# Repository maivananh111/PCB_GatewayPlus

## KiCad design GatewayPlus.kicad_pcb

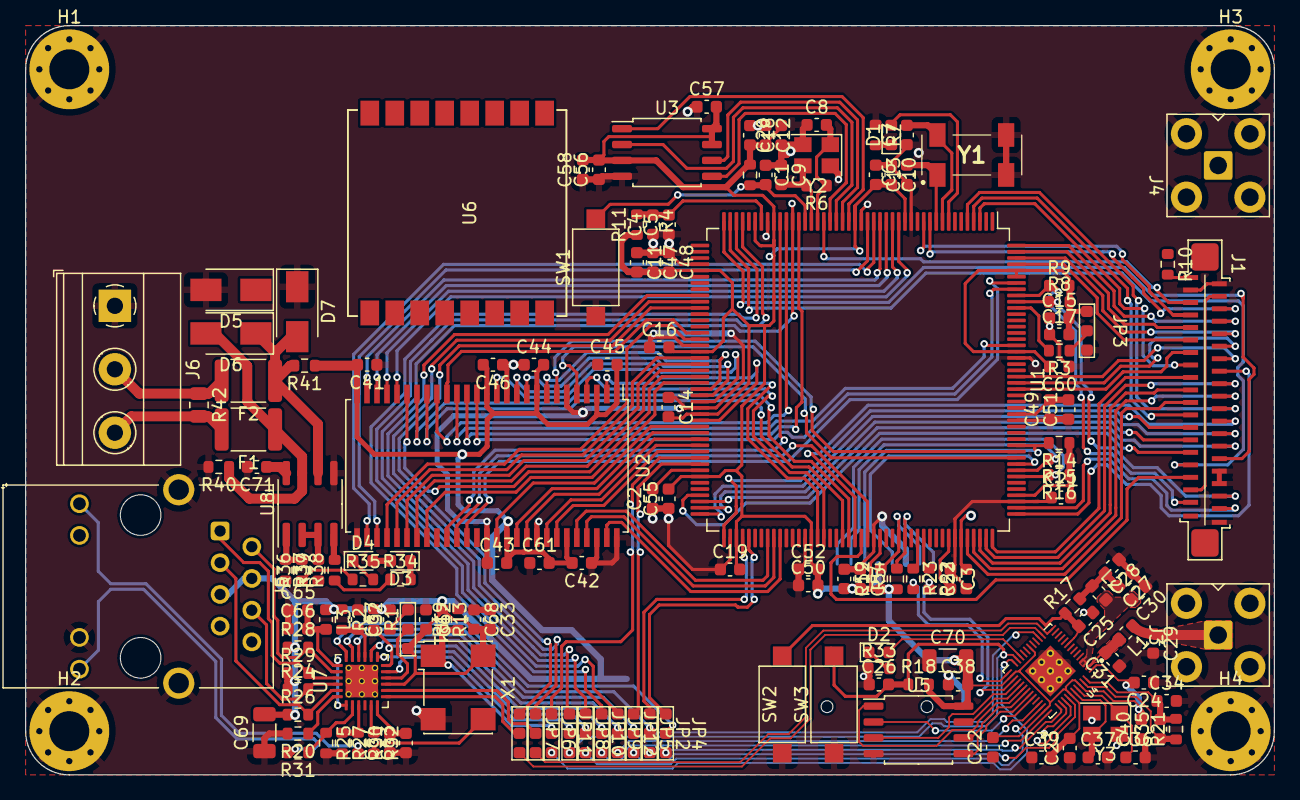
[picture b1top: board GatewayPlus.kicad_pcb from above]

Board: 2 copper layers, 100.0 x 60.0 mm, 162 parts (1 on the bottom side), 172 nets.

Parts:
C1, C2, C3, C4, C5, C8, C9, C25, C26, C32, C33, C62, C63, C64, C65, C66, C67, C68, C71: C_Small; C_0603_1608Metric
C6, C7: 22pF; C_0603_1608Metric
C10, C15, C16, C18, C22, C27, C38, C41, C44, C47, C50, C53, C56, C59: 1uF; C_0603_1608Metric
C11, C12, C13, C14, C17, C19, C20, C21, C23, C24, C28, C29, C30, C31, C34, C35, C36, C37, C39, C40, C42, C43, C45, C46, C48, C49, C51, C52, C54, C55, C57, C58, C60, C61: 100nF; C_0603_1608Metric
C69: C_Small; C_1206_3216Metric
C70: 10uF; C_1206_3216Metric
D1: LED; LED_0603_1608Metric
D2: LED_WIFI; LED_0603_1608Metric
D3: RS_Tx; LED_0603_1608Metric
D4: RS_Rx; LED_0603_1608Metric
D5, D6, D7: D_TVS; D_SMA
F1, F2: Fuse; Fuse_1812_4532Metric
H1, H2, H3, H4: Hole; MountingHole_3.2mm_M3_Pad_Via
J1: LTDC_LCD_FPC_40p; FPC_40p_Vertical
J2: Micro_SD_Card; MicroSD_Socket
J3: ESP Anten; Connector_Coaxial_SMA
J4: xAnt; Connector_Coaxial_SMA
J5: HR911105A; RJ45_Hanrun_HR911105A
J6: RS485; TerminalBlock_Phoenix_MKDS-1,5-3-5.08_1x03_P5.08mm_Horizont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
JP1: PHYADDR; Jump3_0603_Open
JP2: J_TXD0; Jump3_0603_Open
JP3: BOOT; Jump3_0603_Open
JP4: J_TXD1; Jump3_0603_Open
JP5: J_TXEN; Jump3_0603_Open
JP6: J_RXD0; Jump3_0603_Open
JP7: J_RXD1; Jump3_0603_Open
JP8: J_CRS_DV; Jump3_0603_Open
JP9: J_MDIO; Jump3_0603_Open
JP10: J_MDC; Jump3_0603_Open
JP11: J_CLKEN; Jump3_0603_Open
JP12: J_REFCLK; Jump3_0603_Open
L1, L2, L3: L_Small; L_0603_1608Metric
R1, R2, R3, R4, R5, R6, R7, R11, R12, R13, R14, R15, R16, R17, R18, R19, R20, R21, R22, R23, R24, R25, R26, R27, R28, R29, R30, R31, R32, R33, R34, R35, R36, R37, R38, R39, R40, R41: R_Small; R_0603_1608Metric
R8: 4k7; R_0603_1608Metric
R9: 4K7; R_0603_1608Metric
R10: 220; R_0603_1608Metric
R42: 120; R_0805_2012Metric
SW1: SW_Push; SW_SPST_CK_RS282G05A3
SW2: ESP_RESET; SW_SPST_CK_RS282G05A3
SW3: ESP_BOOT; SW_SPST_CK_RS282G05A3
U1: STM32F429IGTx; LQFP-176_24x24mm_P0.5mm
U2: IS42S16400J - HY57V641620E; TSOP-II-54_22.2x10.16mm_P0.8mm
U3: W25Q128JVS; SOIC-8_5.23x5.23mm_P1.27mm
U4: ESP32-D0WD-V3; ESP32-QFN48
U5: W25Q32JVSS; SOIC-8_5.23x5.23mm_P1.27mm
U6: Ai-Thinker-Ra-02; Ai-Thinker-Ra-01-LoRa
U7: LAN8720A; QFN-24-1EP_4x4mm_P0.5mm_EP2.6x2.6mm_ThermalVias
U8: MAX3485; SOIC-8_3.9x4.9mm_P1.27mm
X1: 50MHz; Oscillator_SMD_Abracon_ASV-4Pin_7.0x5.1mm
Y1: 32.768KHz; MC306327680KE3ROHS
Y2: 25MHz; Crystal_SMD_3225-4Pin_3.2x2.5mm
Y3: 40MHz; Crystal_SMD_3225-4Pin_3.2x2.5mm

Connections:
+3.3V: C10.2, C11.2, C12.2, C13.2, C14.2, C15.2, C16.2, C17.2, C18.2, C19.2, C20.2, C21.2, C22.2, C23.2, C24.2, C27.2, C28.2, C33.2, C38.2, C39.2, C40.2, C41.2, C42.2, C43.2, C44.2, C45.2, C46.2, C47.2, C48.2, C49.2, C50.2, C51.2, C52.2, C53.2, C54.2, C55.2, C56.2, C57.2, C58.2, C59.2, C60.2, C61.2, C62.2, C67.2, C68.2, C69.2, C70.2, C71.1, D3.2 (A), D4.2 (A), J1.4 (3V3), J1.35 (3V3), J2.4 (VDD), J5.4, J5.5, JP1.3 (B), JP3.1 (A), L2.1, L3.1, R1.1, R2.1, R4.2, R5.1, R8.2, R9.2, R11.1, R12.1, R13.1, R14.1, R15.1, R16.1, R17.2, R18.2, R24.1, R26.1, R28.1, R29.1, R39.2, R41.1, U1.15 (VDD), U1.23 (VDD), U1.36 (VDD), U1.39 (VDDA), U1.49 (VDD), U1.62 (VDD), U1.72 (VDD), U1.82 (VDD), U1.91 (VDD), U1.103 (VDD), U1.114 (VDD), U1.127 (VDD), U1.136 (VDD), U1.149 (VDD), U1.159 (VDD), U1.171 (PDR_ON), U1.172 (VDD), U2.1 (VDD), U2.3 (VDDQ), U2.9 (VDDQ), U2.14 (VDD), U2.27 (VDD), U2.43 (VDDQ), U2.49 (VDDQ), U3.3 (IO2), U3.7 (IO3), U3.8 (VCC), U4.1 (VDDA), U4.19 (VDD_RTC), U4.26 (VDD_SDIO), U4.37 (VDD_CPU), U4.43 (VDDA), U4.46 (VDDA), U5.8 (VCC), U7.9 (VDDIO), U8.8 (VCC), X1.4 (Vdd)
/ETH/ETH_CLKEN: JP11.2 (C), R13.2, R19.1, X1.1 (EN)
/ETH/ETH_REFCLK: JP12.2 (C), U7.14 (INT/REFCLKO)
/ETH/RMII_CRS_DV: JP8.2 (C), U7.11 (CRS_DV/MODE2)
/ETH/RMII_MDC: JP10.2 (C), U7.13 (MDC)
/ETH/RMII_MDIO: JP9.2 (C), R1.2, U7.12 (MDIO)
/ETH/RMII_RXD0: JP6.2 (C), U7.8 (RXD0/MODE0)
/ETH/RMII_RXD1: JP7.2 (C), U7.7 (RXD1/MODE1)
/ETH/RMII_TXD0: JP2.2 (C), U7.17 (TXD0)
/ETH/RMII_TXD1: JP4.2 (C), U7.18 (TXD1)
/ETH/RMII_TXEN: JP5.2 (C), U7.16 (TXEN)
/LTDC TFT LCD/LCD_BACKGROUND_LED: R10.1, U1.138 (PA15)
/LTDC TFT LCD/LTDC_B0: J1.15 (B0), U1.3 (PE4)
/LTDC TFT LCD/LTDC_B1: J1.14 (B1), U1.155 (PG12)
/LTDC TFT LCD/LTDC_B2: J1.13 (B2), U1.153 (PG10)
/LTDC TFT LCD/LTDC_B3: J1.12 (B3), U1.154 (PG11)
/LTDC TFT LCD/LTDC_B4: J1.11 (B4), U1.173 (PI4)
/LTDC TFT LCD/LTDC_B5: J1.10 (B5), U1.174 (PI5)
/LTDC TFT LCD/LTDC_B6: J1.9 (B6), U1.175 (PI6)
/LTDC TFT LCD/LTDC_B7: J1.8 (B7), U1.176 (PI7)
/LTDC TFT LCD/LTDC_DE: J1.5 (DE), U1.28 (PF10)
/LTDC TFT LCD/LTDC_G0: J1.23 (G0), U1.4 (PE5)
/LTDC TFT LCD/LTDC_G1: J1.22 (G1), U1.5 (PE6)
/LTDC TFT LCD/LTDC_G2: J1.21 (G2), U1.128 (PH13)
/LTDC TFT LCD/LTDC_G3: J1.20 (G3), U1.129 (PH14)
/LTDC TFT LCD/LTDC_G4: J1.19 (G4), U1.130 (PH15)
/LTDC TFT LCD/LTDC_G5: J1.18 (G5), U1.131 (PI0)
/LTDC TFT LCD/LTDC_G6: J1.17 (G6), U1.132 (PI1)
/LTDC TFT LCD/LTDC_G7: J1.16 (G7), U1.133 (PI2)
/LTDC TFT LCD/LTDC_HSYNC: J1.7 (HSYNC), U1.12 (PI10)
/LTDC TFT LCD/LTDC_PCLK: J1.33 (PCLK), U1.111 (PG7)
/LTDC TFT LCD/LTDC_R0: J1.31 (R0), U1.43 (PH2)
/LTDC TFT LCD/LTDC_R1: J1.30 (R1), U1.44 (PH3)
/LTDC TFT LCD/LTDC_R2: J1.29 (R2), U1.85 (PH8)
/LTDC TFT LCD/LTDC_R3: J1.28 (R3), U1.86 (PH9)
/LTDC TFT LCD/LTDC_R4: J1.27 (R4), U1.87 (PH10)
/LTDC TFT LCD/LTDC_R5: J1.26 (R5), U1.88 (PH11)
/LTDC TFT LCD/LTDC_R6: J1.25 (R6), U1.89 (PH12)
/LTDC TFT LCD/LTDC_R7: J1.24 (R7), U1.110 (PG6)
/LTDC TFT LCD/LTDC_VSYNC: J1.6 (VSYNC), U1.11 (PI9)
/LTDC TFT LCD/TOUCH_INT: J1.38 (T_INT), U1.134 (PI3)
/LTDC TFT LCD/TOUCH_SCL: J1.36 (T_SCL), R8.1, U1.167 (PB8)
/LTDC TFT LCD/TOUCH_SDA: J1.37 (T_SDA), R9.1, U1.168 (PB9)
/MCU/ETH_CLKEN: JP11.1 (A), U1.79 (PB10)
/MCU/ETH_REFCLK: JP12.1 (A), U1.41 (PA1)
/MCU/FLASH_CS: U1.24 (PF6), U3.1 (~CS)
/MCU/RMII_CRS_DV: JP8.1 (A), U1.53 (PA7)
/MCU/RMII_MDC: JP10.1 (A), U1.33 (PC1)
/MCU/RMII_MDIO: JP9.1 (A), U1.42 (PA2)
/MCU/RMII_RXD0: JP6.1 (A), U1.54 (PC4)
/MCU/RMII_RXD1: JP7.1 (A), U1.55 (PC5)
/MCU/RMII_TXD0: JP2.1 (A), U1.92 (PB12)
/MCU/RMII_TXD1: JP4.1 (A), U1.93 (PB13)
/MCU/RMII_TXEN: JP5.1 (A), U1.80 (PB11)
/MCU/SDIO_CLK: J2.5 (CLK), U1.141 (PC12)
/MCU/SDIO_CMD: J2.3 (CMD), R14.2, U1.144 (PD2)
/MCU/SDIO_D0: J2.7 (DAT0), R12.2, U1.117 (PC8)
/MCU/SDIO_D1: J2.8 (DAT1), R5.2, U1.118 (PC9)
/MCU/SDIO_D2: J2.1 (DAT2), R16.2, U1.139 (PC10)
/MCU/SDIO_D3: J2.2 (DAT3/CD), R15.2, U1.140 (PC11)
/MCU/SDRAM_A0: U1.16 (PF0), U2.23 (A0)
/MCU/SDRAM_A1: U1.17 (PF1), U2.24 (A1)
/MCU/SDRAM_A2: U1.18 (PF2), U2.25 (A2)
/MCU/SDRAM_A3: U1.19 (PF3), U2.26 (A3)
/MCU/SDRAM_A4: U1.20 (PF4), U2.29 (A4)
/MCU/SDRAM_A5: U1.21 (PF5), U2.30 (A5)
/MCU/SDRAM_A6: U1.60 (PF12), U2.31 (A6)
/MCU/SDRAM_A7: U1.63 (PF13), U2.32 (A7)
/MCU/SDRAM_A8: U1.64 (PF14), U2.33 (A8)
/MCU/SDRAM_A9: U1.65 (PF15), U2.34 (A9)
/MCU/SDRAM_A10: U1.66 (PG0), U2.22 (A10)
/MCU/SDRAM_A11: U1.67 (PG1), U2.35 (A11)
/MCU/SDRAM_BA0: U1.108 (PG4), U2.20 (BA0)
/MCU/SDRAM_BA1: U1.109 (PG5), U2.21 (BA1)
/MCU/SDRAM_CKE: U1.35 (PC3), U2.37 (CKE)
/MCU/SDRAM_CLK: U1.112 (PG8), U2.38 (CLK)
/MCU/SDRAM_D0: U1.104 (PD14), U2.2 (DQ0)
/MCU/SDRAM_D1: U1.105 (PD15), U2.4 (DQ1)
/MCU/SDRAM_D2: U1.142 (PD0), U2.5 (DQ2)
/MCU/SDRAM_D3: U1.143 (PD1), U2.7 (DQ3)
/MCU/SDRAM_D4: U1.68 (PE7), U2.8 (DQ4)
/MCU/SDRAM_D5: U1.69 (PE8), U2.10 (DQ5)
/MCU/SDRAM_D6: U1.70 (PE9), U2.11 (DQ6)
/MCU/SDRAM_D7: U1.73 (PE10), U2.13 (DQ7)
/MCU/SDRAM_D8: U1.74 (PE11), U2.42 (DQ8)
/MCU/SDRAM_D9: U1.75 (PE12), U2.44 (DQ9)
/MCU/SDRAM_D10: U1.76 (PE13), U2.45 (DQ10)
/MCU/SDRAM_D11: U1.77 (PE14), U2.47 (DQ11)
/MCU/SDRAM_D12: U1.78 (PE15), U2.48 (DQ12)
/MCU/SDRAM_D13: U1.96 (PD8), U2.50 (DQ13)
/MCU/SDRAM_D14: U1.97 (PD9), U2.51 (DQ14)
/MCU/SDRAM_D15: U1.98 (PD10), U2.53 (DQ15)
/MCU/SDRAM_NBL0: U1.169 (PE0), U2.15 (LDQM)
/MCU/SDRAM_NBL1: U1.170 (PE1), U2.39 (UDQM)
/MCU/SDRAM_NCAS: U1.160 (PG15), U2.17 (~CAS)
/MCU/SDRAM_NE: U1.34 (PC2), U2.19 (~CS)
/MCU/SDRAM_NRAS: U1.59 (PF11), U2.18 (~RAS)
/MCU/SDRAM_NWE: U1.32 (PC0), U2.16 (~WE)
/MCU/SPI1_MISO: U1.26 (PF8), U3.2 (DO(IO1))
/MCU/SPI1_MOSI: U1.27 (PF9), U3.5 (DI(IO0))
/MCU/SPI1_SCK: U1.25 (PF7), U3.6 (CLK)
/MCU/USART1_RX: R22.1, U1.121 (PA10)
/MCU/USART1_TX: R23.1, U1.120 (PA9)
/RS485/A+: F2.2, J6.2, R42.1
/RS485/B-: F1.2, J6.3, R42.2
/RS485/Rx: R35.1, R36.1
/RS485/Tx: R34.1, R38.1
/WIFI ESP32/ETH_CLKEN: JP11.3 (B), U4.24 (GPIO4)
/WIFI ESP32/ETH_REFCLK: C26.2, JP12.3 (B), R18.1, SW3.2, U4.23 (GPIO0)
/WIFI ESP32/F_CLK: U4.31 (SD_CLK), U5.6 (CLK)
/WIFI ESP32/F_CMD: U4.30 (SD_CMD), U5.1 (~CS)
/WIFI ESP32/F_D0: U4.32 (SD_D0), U5.5 (DI(IO0))
/WIFI ESP32/F_D1: U4.33 (SD_D1), U5.2 (DO(IO1))
/WIFI ESP32/F_D2: U4.28 (SD_D2), U5.3 (IO2)
/WIFI ESP32/F_D3: U4.29 (SD_D3), U5.7 (IO3)
/WIFI ESP32/RMII_CRSDV: JP8.3 (B), U4.16 (GPIO27)
/WIFI ESP32/RMII_MDC: JP10.3 (B), U4.36 (GPIO23)
/WIFI ESP32/RMII_MDIO: JP9.3 (B), U4.35 (GPIO18)
/WIFI ESP32/RMII_RXD0: JP6.3 (B), U4.14 (GPIO25)
/WIFI ESP32/RMII_RXD1: JP7.3 (B), U4.15 (GPIO26)
/WIFI ESP32/RMII_TXD0: JP2.3 (B), U4.38 (GPIO19)
/WIFI ESP32/RMII_TXD1: JP4.3 (B), U4.39 (GPIO22)
/WIFI ESP32/RMII_TXEN: JP5.3 (B), U4.42 (GPIO21)
BOOT0: JP3.2 (C), R3.1
GND: C1.1, C2.1, C3.1, C4.1, C5.1, C6.1, C7.1, C8.1, C9.1, C10.1, C11.1, C12.1, C13.1, C14.1, C15.1, C16.1, C17.1, C18.1, C19.1, C20.1, C21.1, C22.1, C23.1, C24.1, C25.1, C26.1, C27.1, C28.1, C29.2, C30.1, C31.1, C32.1, C33.1, C34.2, C36.2, C37.2, C38.1, C39.1, C40.1, C41.1, C42.1, C43.1, C44.1, C45.1, C46.1, C47.1, C48.1, C49.1, C50.1, C51.1, C52.1, C53.1, C54.1, C55.1, C56.1, C57.1, C58.1, C59.1, C60.1, C61.1, C62.1, C63.1, C64.1, C65.1, C66.1, C67.1, C68.1, C69.1, C70.1, C71.2, D5.2 (A2), D7.1 (A1), H1.1, H2.1, H3.1, H4.1, J1.2 (LED-), J1.3 (GND), J1.32 (GND), J1.34 (GND), J1.40 (GND), J2.6 (VSS), J2.9 (SHIELD), J3.2 (Ext), J4.2 (Ext), J5.8, J5.11, J5.SH (SHIELD), J6.1, JP1.1 (A), JP3.3 (B), R7.1, R19.2, R20.2, R25.2, R27.2, R33.1, R40.2, SW1.1, SW2.1, SW3.1, U1.14 (VSS), U1.22 (VSS), U1.37 (VSSA), U1.48 (BYPASS_REG), U1.61 (VSS), U1.71 (VSS), U1.90 (VSS), U1.102 (VSS), U1.113 (VSS), U1.126 (VSS), U1.135 (VSS), U1.148 (VSS), U1.158 (VSS), U2.6 (GNDQ), U2.12 (GNDQ), U2.28 (GND), U2.41 (GND), U2.46 (GNDQ), U2.52 (GNDQ), U2.54 (GND), U3.4 (GND), U4.49 (GND_PAD), U5.4 (GND), U7.25 (VSS), U8.5 (GND), X1.2 (GND), Y1.2, Y1.3, Y2.2, Y2.4, Y3.2, Y3.4
HSEI: C8.2, R6.1, U1.29 (PH0), Y2.1
HSEO: C9.2, R6.2, U1.30 (PH1), Y2.3
LSEI: C7.2, U1.9 (PC14), Y1.4
LSEO: C6.2, U1.10 (PC15), Y1.1
unnamed: C1.2, R4.1, SW1.2, U1.31 (NRST)
unnamed: C2.2, U1.81 (VCAP_1)
unnamed: C3.2, U1.125 (VCAP_2)
unnamed: C4.2, C5.2, R11.2, U1.38 (VREF+)
unnamed: C25.2, R17.1, SW2.2, U4.9 (CHIP_PU)
unnamed: C29.1, J3.1 (In), L1.1
unnamed: C30.2, L2.2, U4.3 (VDD), U4.4 (VDD)
unnamed: C31.2, L1.2, U4.2 (LNA_IN)
unnamed: C32.2, R2.2, U7.15 (RST)
unnamed: C34.1, C35.2, R21.2, U4.48 (CAP1)
unnamed: C35.1, R21.1, U4.47 (CAP2)
unnamed: C36.1, U4.45 (XTAL_P), Y3.1
unnamed: C37.1, U4.44 (XTAL_N), Y3.3
unnamed: C63.2, C64.2, U7.6 (VDDCR)
unnamed: C65.2, C66.2, L3.2, U7.1 (VDD2A), U7.19 (VDD1A)
unnamed: D1.1 (K), R7.2
unnamed: D2.1 (K), R33.2
unnamed: D2.2 (A), U4.22 (GPIO2)
unnamed: D3.1 (K), R34.2
unnamed: D4.1 (K), R35.2
unnamed: D5.1 (A1), D6.2 (A2), F1.1, R40.1, U8.7 (B)
unnamed: D6.1 (A1), D7.2 (A2), F2.1, R41.2, U8.6 (A)
unnamed: J1.1 (LED+), R10.2
unnamed: J5.1, R29.2, U7.21 (TXP)
unnamed: J5.2, R28.2, U7.20 (TXN)
unnamed: J5.3, R26.2, U7.23 (RXP)
unnamed: J5.6, R24.2, U7.22 (RXN)
unnamed: J5.9, R30.2
unnamed: J5.12, R31.2
unnamed: JP1.2 (C), U7.10 (RXER/PHYAD0)
unnamed: R3.2, U1.166 (BOOT0)
unnamed: R20.1, U7.24 (RBIAS)
unnamed: R22.2, U4.27 (GPIO17)
unnamed: R23.2, U4.25 (GPIO16)
unnamed: R25.1, R31.1, U7.2 (LED2/nINTSEL)
unnamed: R27.1, R30.1, U7.3 (LED1/REGOFF)
unnamed: R32.1, U7.5 (XTAL1/CLKIN)
unnamed: R32.2, X1.3 (OUT)
unnamed: R36.2, R39.1, U8.1 (RO)
unnamed: R37.2, U8.2 (~RE), U8.3 (DE)
unnamed: R38.2, U8.4 (DI)
unnamed: U6.1 (GND), U6.2 (GND), U6.9 (GND), U6.16 (GND)
STATUS LED: D1.2 (A), U1.8 (PC13)

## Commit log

2023-02-06 MCU, FLASH, SDRAM, LCD.
2023-02-09 Add WiFi block and finished WiFi layout
2023-02-10 Add Ethernet LAN8720 Layout.
2023-02-11 Finish Ethernet Layout.
2023-02-11 Add RS485 Layout.
